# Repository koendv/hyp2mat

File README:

hyp2mat

hyp2mat is a utility which converts HyperLynx files to matlab for electromagnetic simulation, or to PDF for printing.
hyp2mat is distributed with openEMS (http://www.openems.de), a free open-source electromagnetic field solver.

 Installation

hyp2mat can be installed from pre-compiled binaries, or compiled from source:

* Windows binaries ( http://www.kdvelectronics.eu/hyp2mat/hyp2mat-win32-current.zip )
* Linux packages ( https://build.opensuse.org/package/show?package=hyp2mat&project=home%3Asibbi77 )
* To install from source see the file INSTALL for compilation instructions

 Tutorial

How to simulate a printed circuit board in openEMS using HyperLynx files ( http://openems.de/index.php/Tutorial:_Importing_with_hyp2mat ) 

 See also

hyp2mat is command-line only. For graphical, menu-driven Hyperlynx import see 

* pcb-rnd, a printed circuit board editor. ( http://repo.hu/projects/pcb-rnd/ )
* FreeCAD-PCB, for import into FreeCAD. ( https://eaglepcb2freecad.sourceforge.io/ )

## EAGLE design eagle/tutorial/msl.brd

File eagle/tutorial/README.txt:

Tutorial for hyp2mat.

To run the demo, first install and configure matlab or octave, CSXCAD, openEMS and hyp2mat. 
Copy the tutorial files to a directory where you have read and write access.
Start up matlab or octave from that directory, and type 'tutorial_hyp2mat'.
When the AppCSXCAD window appears, exit AppCSXCAD.
After a few minutes simulation output should appear.

Further documentation is at http://www.openems.de, under "Tutorial: Importing with hyp2mat"

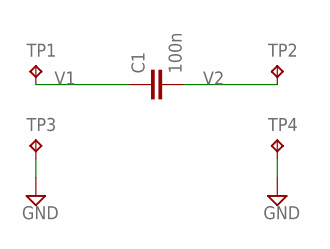
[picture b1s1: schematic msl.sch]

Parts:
C1: 100n; C0402K
TP1, TP2, TP3, TP4: TPTP06SQ; TP06SQ

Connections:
GND: TP3.TP, TP4.TP
V1: C1.1, TP1.TP
V2: C1.2, TP2.TP

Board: 2 copper layers, 5 parts (2 on the bottom side), 3 nets, no tracks yet.

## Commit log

2012-11-09 first public version
2012-11-10 added Makefile targets tarball and install
2012-11-10 updated .gitignore
2012-11-10 fixed permission problem (install rule)
2012-11-10 Update INSTALL
    Update INSTALL with hyperlynx.ulp url
2012-11-13 Move to using DetectEdges/SmoothMesh
2012-11-14 fix demo_notch.m thorsten
2012-11-14 auto smooth demo mesh
2012-11-14 fix dielectric height
2012-11-14 fix plot scale
2012-11-14 dielectric epsilon_r spec
2012-11-15 replace isstr() with ischar()
2012-11-15 eagle 6.3
2012-11-15 first release candidate
2012-11-16 update comments
2012-11-16 copper thickness update
2012-11-16 packaging
2012-11-16 Makefile change to accommodate recent directory layout changes
2012-11-27 win32: fixes for win32 support
2012-11-28 demo epsilonr fix; speedup
2012-11-28 swap pics
2012-11-29 debug output
2012-12-04 Tutorial
2012-12-04 fix rotation
2012-12-04 fix rotation of pads
2012-12-05 bump version to 0.0.3
2012-12-05 remove rotate
2012-12-05 cleanup
2012-12-11 bump
2012-12-17 polygon arithmetic
2012-12-18 joining polygons
2012-12-18 add devices
2013-03-26 c++ version
2013-03-27 csxcad: assume metal layer thickness negligible
2013-03-27 force metal layers zero thickness
2013-03-28 support layered dielectrics
2013-03-30 align pins to grid
2013-03-31 dielectric with AddBox
2013-04-01 doc update
2013-04-01 add port centre coordinates
2013-04-01 cppcheck
2013-04-01 add option to set epsilon
2013-04-01 cropping board
2013-04-02 fix parser includes
2013-04-02 update doc
2013-04-02 cleanup examples and doc
2013-04-02 invert planes
2013-04-02 cleanup doc
2013-04-03 document error messages
2013-04-04 add manual in pdf for Windows users
2013-04-04 win32 compilation instructions
2013-04-04 markdown
2013-04-04 to satisfy autoconf
2013-04-05 improve windows doc
2013-04-07 separate library and prog
2013-04-08 build fix
2013-04-08 increase arc accuracy
2013-04-09 plane separation
2013-04-10 add plane separation
2013-05-15 polygon math, part 1
2013-05-17 ensure polygon ids do not clash
2013-05-18 improve board edge algorithm
2013-05-18 add --layer to doc
2013-05-24 adjust cropping
2013-07-18 AddHyperLynxComponent
2013-07-21 AddHyperLynxComponent hor/ver
2013-07-27 Matlab compatibility fix: clear LD_LIBRARY_PATH for system command
2013-07-29 add AddHyperLynxComponent.m to Makefile.in
2013-07-29 win32 build script
2013-07-29 configure.ac version 0.0.6
2013-07-29 update version number in doc
2013-08-01 mingw update
2013-08-28 padstack MDEF & ADEF layers fix
2013-08-29 crop and padstack fixes
2013-09-05 polygon arc orientation fix
2013-09-06 add clearance param
2013-09-09 epsilon r override command line parameter
2013-09-09 warn on PLANE layer or PLANE polygon
2013-09-09 mark
2013-09-10 flood copper planes
2013-09-12 plane layers
2013-09-13 version bump
2013-09-13 matlab: use searchBinary from CSXCAD to find hyp2mat binary
2013-09-16 bugfix: padstack end
2013-10-01 automake cleanup
2013-10-03 code cleanup
2013-10-04 copper
2013-10-09 fix plane layers
2013-10-09 fix crop
2013-10-09 flood command line option
2013-10-11 plane separation calculation
2013-10-11 update comment
2013-10-11 comment
2013-10-15 clean generated files from git repo
2013-10-15 added makefile targets: tarball and tarball-dist
2013-10-16 fix comment
2013-10-16 makefile.am update
2013-10-17 repo generated files cleanup
2013-10-17 don't call aclocal; use autoreconf
2013-10-17 create m4 dir
2013-10-22 --flood option per layer
2013-10-22 parse.h dependency
2013-10-25 check libtool first
2013-10-25 generated doc files
2013-10-25 AddBox instead of AddLinPoly
2013-10-25 hyp2mat v0.0.10
2013-10-25 add comment
2013-10-29 detailed board outline
2013-11-17 Clipperlib 6.0.0 upgrade
2013-12-23 rollback to ClipperLIb 5.1.6
2013-12-23 add ClipperLib version no to debug output
2014-01-26 polygon hole bugfix. option to model copper as lossy or as perfect conductor
2014-01-26 new option: lossy copper
2014-01-27 add dielectric conductivity
2014-02-06 Customizing dielectric models
2014-02-06 update demo runtime
2014-02-06 update demos
2014-03-01 update lossy dielectric
2014-03-01 v 0.0.13
2014-07-21 adapt Makefile for both bison 2.x and 3.x
2014-07-22 add gerber options
2014-07-24 create gerbv project
2014-07-25 allow multiple excellon drill files
2014-07-27 flex output
2014-07-29 import gerber drills
2014-08-02 gerber: add default board outline
2014-08-03 gerber: naming layers
2014-08-05 cairo-clipper interface
2014-08-08 add gerbv draw code
2014-08-08 gerbv
2014-08-14 patch gerbv
2014-08-15 add default border, pdf using cairo
2014-08-15 draw via bug
2014-08-15 pdf via centre
2014-08-18 credits
2014-08-19 add libgerbv source
2014-08-19 error msg fix
2014-08-19 add patch
2014-08-19 win32 doc
2014-08-19 drop hpdf include
2014-08-19 update build instr
2014-08-19 win32 notes
2014-08-21 usage
2014-08-26 reorg clipper src
2015-02-19 add board outline if board outline not defined
2015-02-22 blind and buried vias
2015-04-07 back to the future :)
2015-04-16 add 3d metal option
2015-04-29 option: 3d metal
2015-04-29 bump version
2015-04-30 fix metal-3d
2015-05-14 add --metal-3d option
2015-08-02 add dll
2017-04-10 pcb-rnd
2017-04-11 pcb-rnd plugin
2017-07-18 backport
2017-07-18 win binaries
2017-07-24 see also pcb-rnd
2017-07-25 new hyperynx ulp
2017-07-26 device VAL= more lenient
2017-07-26 devices
2020-07-16 add QucsStudio pcb format
2020-07-22 qucsstudio
